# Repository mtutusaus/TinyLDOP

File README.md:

# TinyLAB: TinyLDOP

TinyLDOP is a breadboard-compatible linear regulator PCB for generating additional low-current voltage rails from a single power supply. It designed to be placed at the middle part of a breadboard as shown:

---
# **Specifications**
Considering the typical supply voltages of electronic systems, we will set the output voltage range to 1.8 – 12 V. 

According to the LM317M datasheet, the difference between input and output voltage can be as low as 2.5 V. Therefore, the input voltage range must be 4.3 – 14.5 V (which we will round to 5 – 15 V)

The maximum output current depends on the input-output voltage difference and the maximum power the device is able to dissipate. Taking into account the worst case: input voltage equal to 15 V, output voltage equal to 1.8 V and considering the package is able to dissipate 750 mW with a small heatsink, the maximum output current is 57 mA, which we will round to 50 mA.

| Specification       | Value                      |
|---------------|----------------------------------|
| Input voltage range [V]  | 5–15 |
| Output voltage range [V]        | 1.8–12  |
| Maximum output current [mA]         | 50  |

---
## **License**
This project is licensed under the [Creative Commons Attribution-NonCommercial-ShareAlike 4.0 International License](http://creativecommons.org/licenses/by-nc-sa/4.0/).

You are free to:
- **Share** — copy and redistribute the material in any medium or format
- **Adapt** — remix, transform, and build upon the material

Under the following terms:
- **Attribution** — You must give appropriate credit
- **NonCommercial** — You may not use the material for commercial purposes
- **ShareAlike** — Derivatives must use the same license

See the [LICENSE](LICENSE) file for the full license text.

---
## Author

[Miquel Tutusaus](https://github.com/mtutusaus), 2024

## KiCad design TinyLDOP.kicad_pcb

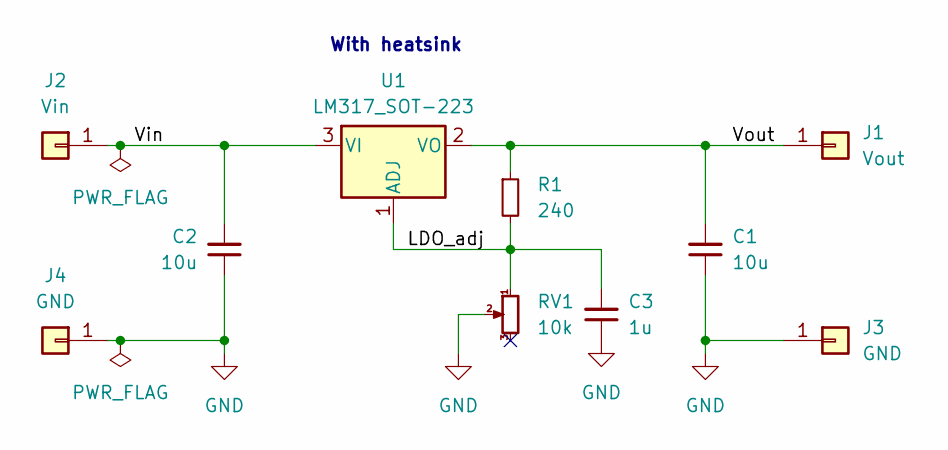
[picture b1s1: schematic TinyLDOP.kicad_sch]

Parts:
C1, C2: 10u; C_1210_3225Metric_Pad1.33x2.70mm_HandSolder
C3: 1u; R_0805_2012Metric_Pad1.20x1.40mm_HandSolder
J1: Vout; PinHeader_1x01_P2.54mm_Vertical
J2: Vin; PinHeader_1x01_P2.54mm_Vertical
J3, J4: GND; PinHeader_1x01_P2.54mm_Vertical
R1: 240; R_0805_2012Metric_Pad1.20x1.40mm_HandSolder
RV1: 10k; Potentiometer_Bourns_3266W_Vertical
U1: LM317_SOT-223; SOT-223-3_TabPin2

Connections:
/LDO_adj: C3.2, R1.2, RV1.1, U1.1 (ADJ)
/Vin: C2.2, J2.1, U1.3 (VI)
/Vout: C1.2, J1.1, R1.1, U1.2 (VO)
GND: C1.1, C2.1, C3.1, J3.1, J4.1, RV1.2

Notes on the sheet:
With heatsink

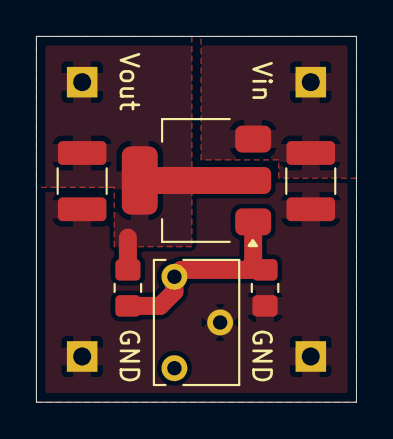
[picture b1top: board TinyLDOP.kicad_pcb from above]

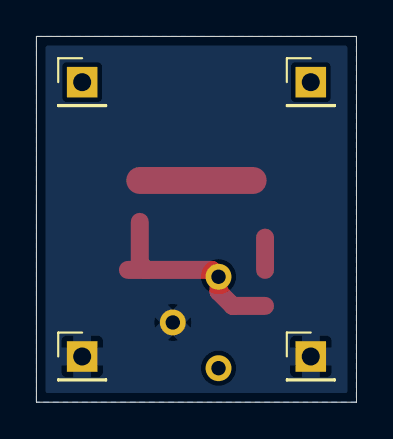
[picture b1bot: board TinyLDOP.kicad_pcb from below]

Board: 2 copper layers, 17.8 x 20.3 mm, 10 parts (4 on the bottom side), 4 nets.
